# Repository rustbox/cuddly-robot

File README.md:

# cuddly-robot

setup: install [minipro](https://gitlab.com/DavidGriffith/minipro)

flash me with `make generate && minipro -p ATF22V10C -w GAL22V10_fifo_buf.jed`

https://www.proto-advantage.com/store/product_info.php?products_id=2200264

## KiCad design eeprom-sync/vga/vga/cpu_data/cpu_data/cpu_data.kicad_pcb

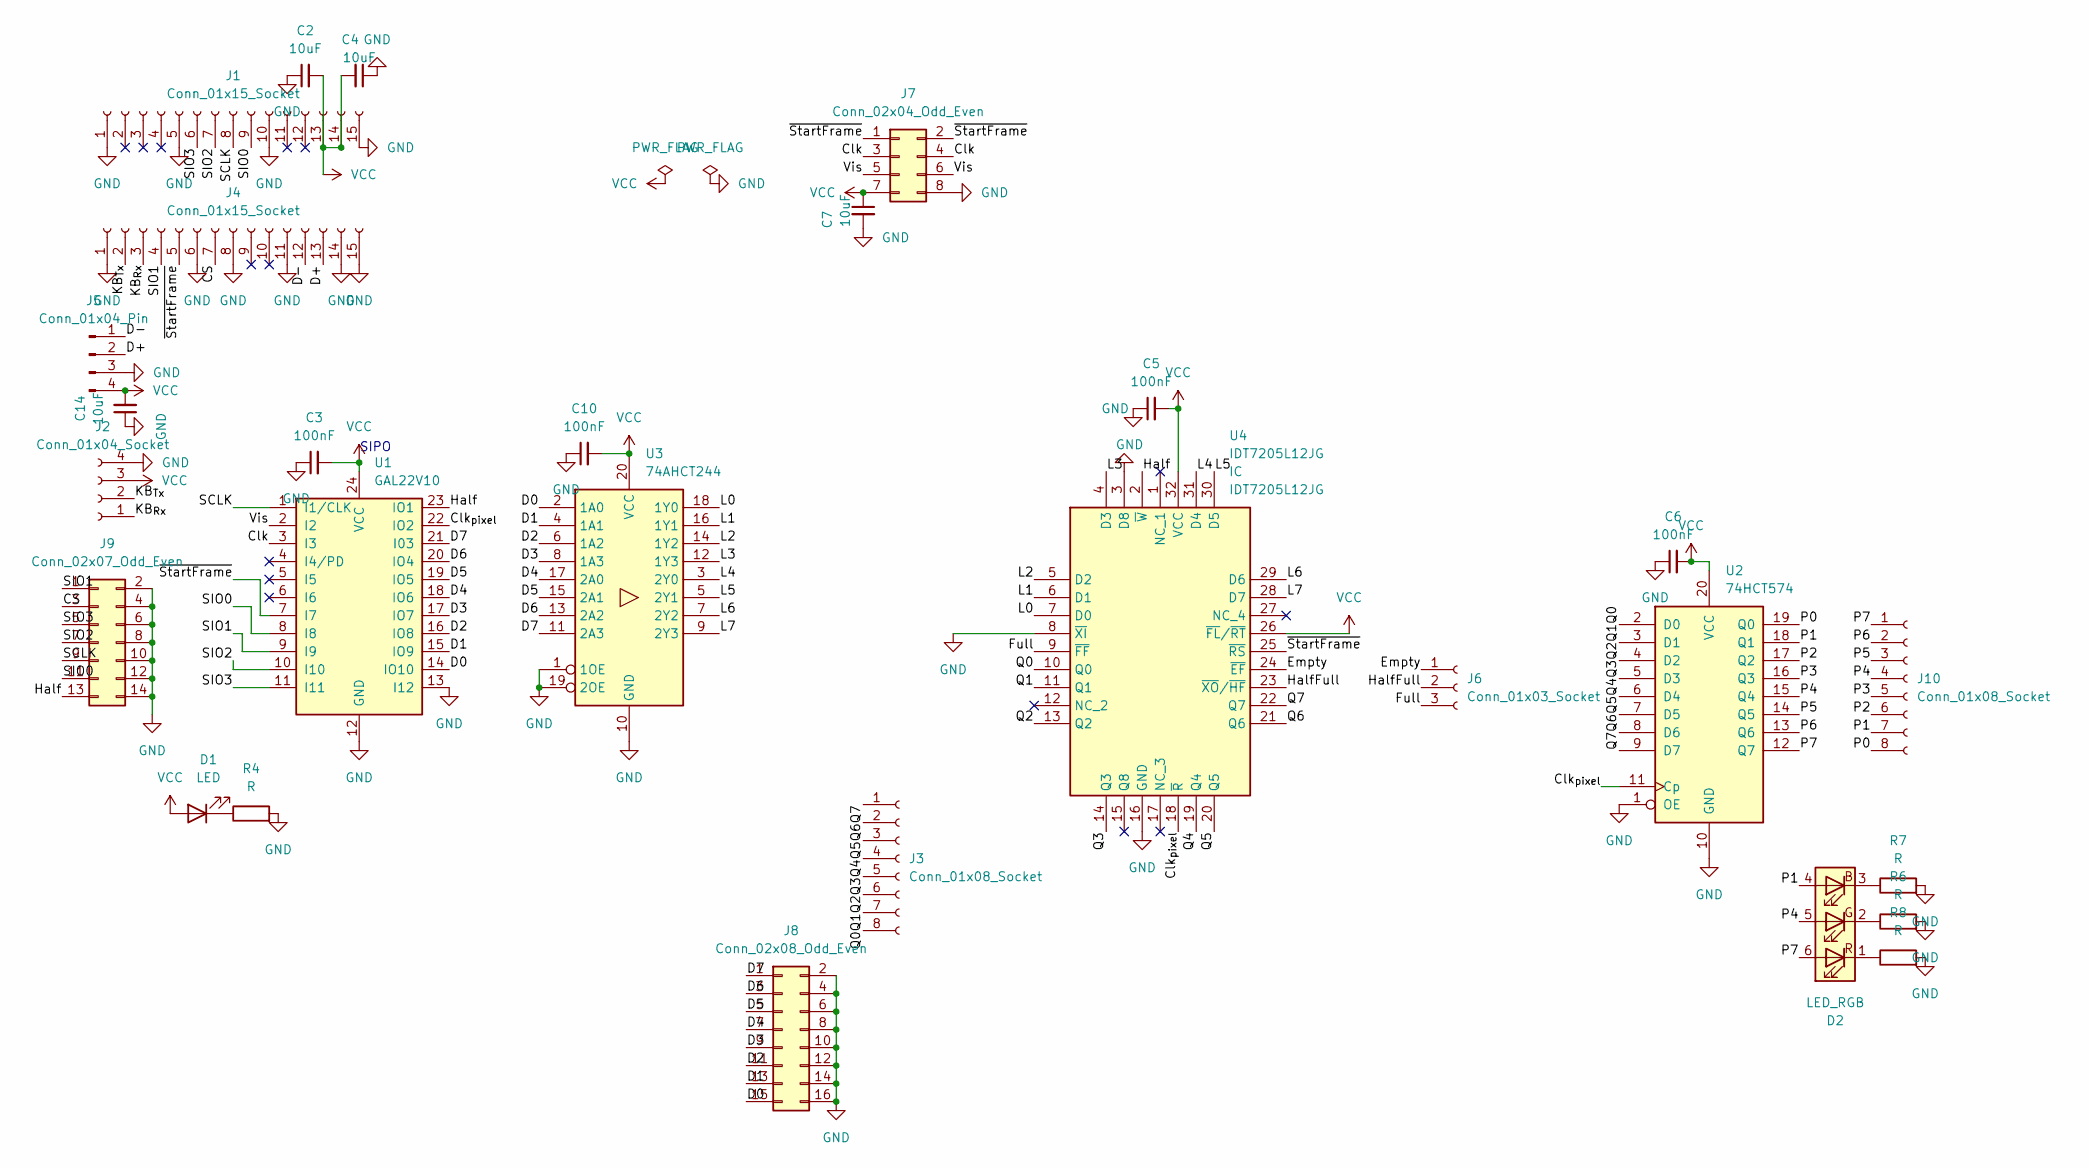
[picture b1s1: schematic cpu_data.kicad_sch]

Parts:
C2, C4, C7, C14: 10uF; C_0805_2012Metric_Pad1.18x1.45mm_HandSolder
C3, C5, C6, C10: 100nF; C_0805_2012Metric_Pad1.18x1.45mm_HandSolder
D1: LED; LED_0805_2012Metric_Pad1.15x1.40mm_HandSolder
D2: LED_RGB; LED_Avago_PLCC6_3x2.8mm
J1, J4: Conn_01x15_Socket; PinSocket_1x15_P2.54mm_Vertical
J2: Conn_01x04_Socket; PinSocket_1x04_P2.54mm_Vertical
J3: Conn_01x08_Socket; PinHeader_1x08_P2.54mm_Vertical
J5: Conn_01x04_Pin; PinHeader_1x04_P2.54mm_Vertical
J6: Conn_01x03_Socket; PinSocket_1x03_P2.54mm_Vertical
J7: Conn_02x04_Odd_Even; PinSocket_2x04_P2.54mm_Vertical
J8: Conn_02x08_Odd_Even; PinHeader_2x08_P2.54mm_Vertical
J9: Conn_02x07_Odd_Even; PinHeader_2x07_P2.54mm_Vertical
J10: Conn_01x08_Socket; PinSocket_1x08_P2.54mm_Vertical
R4, R6, R7, R8: R; R_0805_2012Metric_Pad1.20x1.40mm_HandSolder
U1: GAL22V10; DIP-24_W7.62mm_Socket
U2: 74HCT574; SOIC-20W_7.5x12.8mm_P1.27mm
U3: 74AHCT244; TSSOP-20_4.4x6.5mm_P0.65mm
U4: IDT7205L12JG; plcc32-socket; Manufacturer_Part_Number IDT7205L12JG

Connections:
/CS: J4.7, J9.3
/Clk: J7.3, J7.4, U1.3 (I3)
/Clk_{pixel}: U1.22 (IO2), U2.11 (Cp), U4.18 (~R)
/D0: J8.15, U1.14 (IO10), U3.2 (1A0)
/D1: J8.13, U1.15 (IO9), U3.4 (1A1)
/D2: J8.11, U1.16 (IO8), U3.6 (1A2)
/D3: J8.9, U1.17 (IO7), U3.8 (1A3)
/D4: J8.7, U1.18 (IO6), U3.17 (2A0)
/D5: J8.5, U1.19 (IO5), U3.15 (2A1)
/D6: J8.3, U1.20 (IO4), U3.13 (2A2)
/D7: J8.1, U1.21 (I03), U3.11 (2A3)
/D+: J4.13, J5.2
/D-: J4.12, J5.1
/Empty: J6.1, U4.24 (~EF)
/Full: J6.3, U4.9 (~FF)
/Half: J9.13, U1.23 (IO1), U4.2 (~W)
/HalfFull: J6.2, U4.23 (~XO/~HF)
/KB_{Rx}: J2.1, J4.3
/KB_{Tx}: J2.2, J4.2
/L0: U3.18 (1Y0), U4.7 (D0)
/L1: U3.16 (1Y1), U4.6 (D1)
/L2: U3.14 (1Y2), U4.5 (D2)
/L3: U3.12 (1Y3), U4.4 (D3)
/L4: U3.3 (2Y0), U4.31 (D4)
/L5: U3.5 (2Y1), U4.30 (D5)
/L6: U3.7 (2Y2), U4.29 (D6)
/L7: U3.9 (2Y3), U4.28 (D7)
/P0: J10.8, U2.19 (Q0)
/P1: D2.4 (BA), J10.7, U2.18 (Q1)
/P2: J10.6, U2.17 (Q2)
/P3: J10.5, U2.16 (Q3)
/P4: D2.5 (GA), J10.4, U2.15 (Q4)
/P5: J10.3, U2.14 (Q5)
/P6: J10.2, U2.13 (Q6)
/P7: D2.6 (RA), J10.1, U2.12 (Q7)
/Q0: J3.8, U2.2 (D0), U4.10 (Q0)
/Q1: J3.7, U2.3 (D1), U4.11 (Q1)
/Q2: J3.6, U2.4 (D2), U4.13 (Q2)
/Q3: J3.5, U2.5 (D3), U4.14 (Q3)
/Q4: J3.4, U2.6 (D4), U4.19 (Q4)
/Q5: J3.3, U2.7 (D5), U4.20 (Q5)
/Q6: J3.2, U2.8 (D6), U4.21 (Q6)
/Q7: J3.1, U2.9 (D7), U4.22 (Q7)
/SCLK: J1.8, J9.9, U1.1 (I1/CLK)
/SIO0: J1.9, J9.11, U1.8 (I8)
/SIO1: J4.4, J9.1, U1.9 (I9)
/SIO2: J1.7, J9.7, U1.10 (I10)
/SIO3: J1.6, J9.5, U1.11 (I11)
/Vis: J7.5, J7.6, U1.2 (I2)
/~StartFrame: J4.5, J7.1, J7.2, U1.7 (I7), U4.25 (~RS)
GND: C2.1, C3.1, C4.1, C5.1, C6.1, C7.2, C10.1, C14.1, J1.1, J1.5, J1.10, J1.15, J2.4, J4.1, J4.6, J4.8, J4.11, J4.14, J4.15, J5.3, J7.8, J8.2, J8.4, J8.6, J8.8, J8.10, J8.12, J8.14, J8.16, J9.2, J9.4, J9.6, J9.8, J9.10, J9.12, J9.14, R4.2, R6.2, R7.2, R8.2, U1.12 (GND), U1.13 (I12), U2.1 (OE), U2.10 (GND), U3.1 (1OE), U3.10 (GND), U3.19 (2OE), U4.3 (D8), U4.8 (~XI), U4.16 (GND)
unnamed: D1.1 (K), R4.1
unnamed: D2.3 (BK), R7.1
unnamed: D2.2 (GK), R6.1
unnamed: D2.1 (RK), R8.1
VCC: C2.2, C3.2, C4.2, C5.2, C6.2, C7.1, C10.2, C14.2, D1.2 (A), J1.13, J1.14, J2.3, J5.4, J7.7, U1.24 (VCC), U2.20 (VCC), U3.20 (VCC), U4.26 (~FL/~RT), U4.32 (VCC)

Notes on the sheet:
SIPO

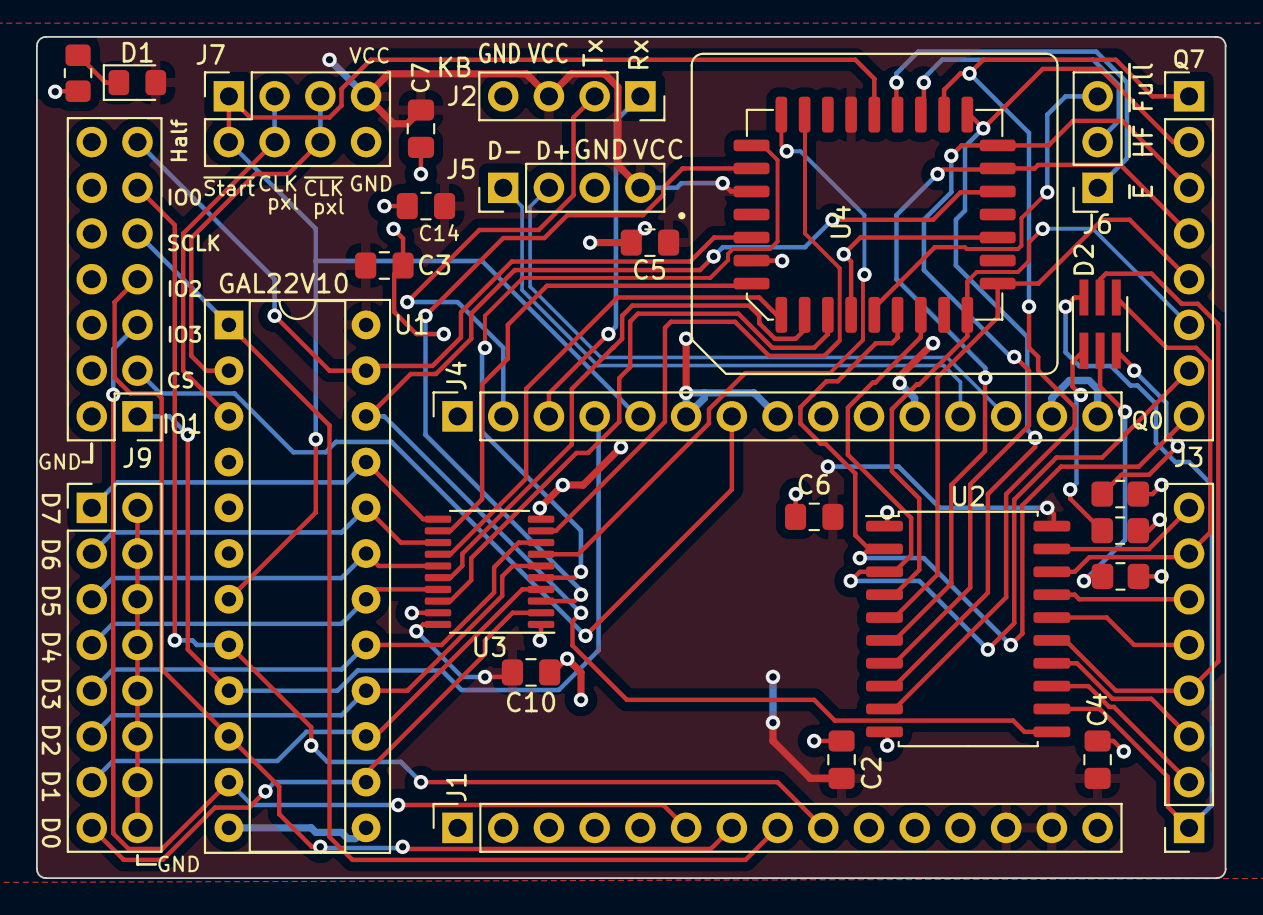
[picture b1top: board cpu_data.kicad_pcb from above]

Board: 2 copper layers, 66.0 x 46.7 mm, 28 parts (0 on the bottom side), 56 nets.

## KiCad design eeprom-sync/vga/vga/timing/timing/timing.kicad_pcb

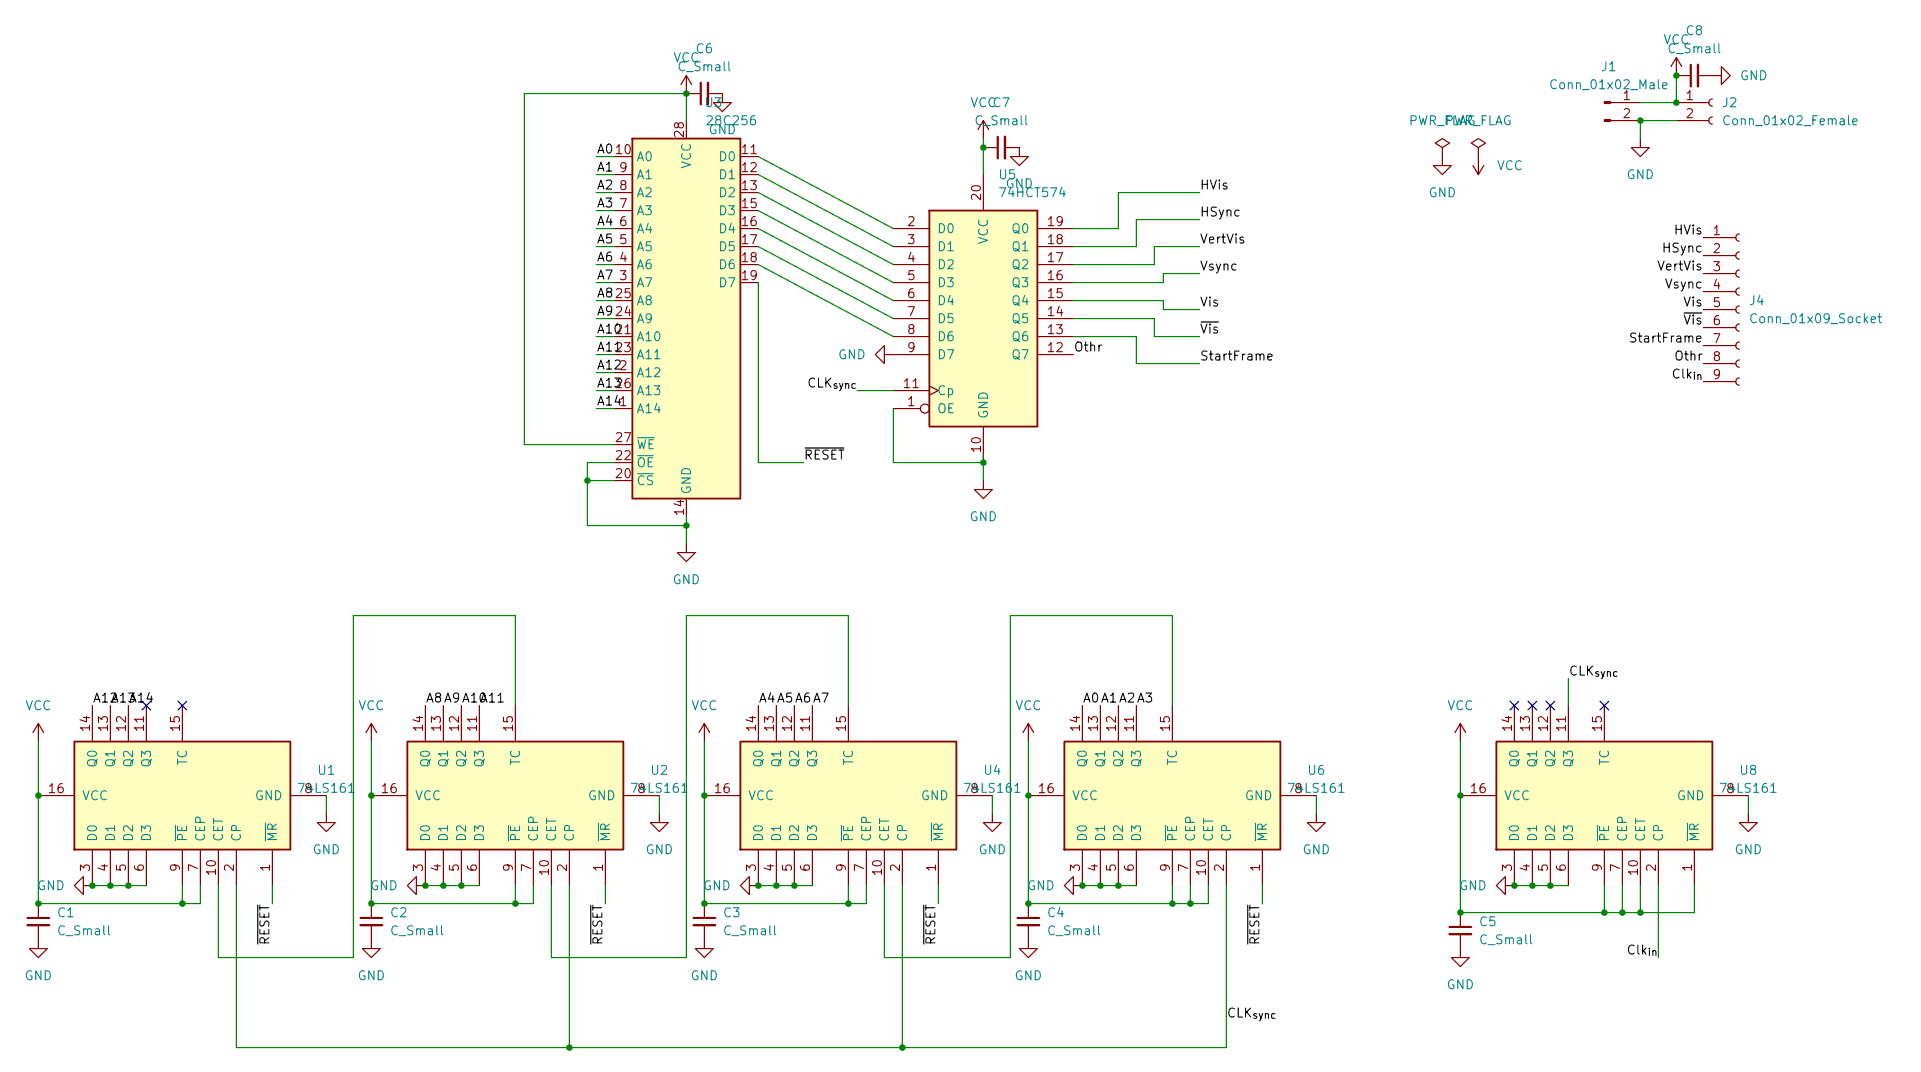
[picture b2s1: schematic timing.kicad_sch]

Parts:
C1, C2, C3, C4, C5, C6, C7, C8: C_Small; C_0805_2012Metric_Pad1.18x1.45mm_HandSolder
J1: Conn_01x02_Male; PinHeader_1x02_P2.54mm_Vertical
J2: Conn_01x02_Female; PinSocket_1x02_P2.54mm_Vertical
J4: Conn_01x09_Socket; PinSocket_1x09_P2.54mm_Vertical
U1, U2, U4, U6, U8: 74LS161; SOIC-16_3.9x9.9mm_P1.27mm
U3: 28C256; DIP-28_W15.24mm_Socket
U5: 74HCT574; SOIC-20W_7.5x12.8mm_P1.27mm

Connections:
/A0: U3.10 (A0), U6.14 (Q0)
/A1: U3.9 (A1), U6.13 (Q1)
/A2: U3.8 (A2), U6.12 (Q2)
/A3: U3.7 (A3), U6.11 (Q3)
/A4: U3.6 (A4), U4.14 (Q0)
/A5: U3.5 (A5), U4.13 (Q1)
/A6: U3.4 (A6), U4.12 (Q2)
/A7: U3.3 (A7), U4.11 (Q3)
/A8: U2.14 (Q0), U3.25 (A8)
/A9: U2.13 (Q1), U3.24 (A9)
/A10: U2.12 (Q2), U3.21 (A10)
/A11: U2.11 (Q3), U3.23 (A11)
/A12: U1.14 (Q0), U3.2 (A12)
/A13: U1.13 (Q1), U3.26 (A13)
/A14: U1.12 (Q2), U3.1 (A14)
/CLK_{sync}: U1.2 (CP), U2.2 (CP), U4.2 (CP), U5.11 (Cp), U6.2 (CP), U8.11 (Q3)
/Clk_{in}: J4.9, U8.2 (CP)
/HSync: J4.2, U5.18 (Q1)
/HVis: J4.1, U5.19 (Q0)
/Othr: J4.8, U5.12 (Q7)
/StartFrame: J4.7, U5.13 (Q6)
/VertVis: J4.3, U5.17 (Q2)
/Vis: J4.5, U5.15 (Q4)
/Vsync: J4.4, U5.16 (Q3)
/~RESET: U1.1 (~MR), U2.1 (~MR), U3.19 (D7), U4.1 (~MR), U6.1 (~MR)
/~Vis: J4.6, U5.14 (Q5)
GND: C1.2, C2.2, C3.2, C4.2, C5.2, C6.2, C7.2, C8.2, J1.2, J2.2, U1.3 (D0), U1.4 (D1), U1.5 (D2), U1.6 (D3), U1.8 (GND), U2.3 (D0), U2.4 (D1), U2.5 (D2), U2.6 (D3), U2.8 (GND), U3.14 (GND), U3.20 (~CS), U3.22 (~OE), U4.3 (D0), U4.4 (D1), U4.5 (D2), U4.6 (D3), U4.8 (GND), U5.1 (OE), U5.9 (D7), U5.10 (GND), U6.3 (D0), U6.4 (D1), U6.5 (D2), U6.6 (D3), U6.8 (GND), U8.3 (D0), U8.4 (D1), U8.5 (D2), U8.6 (D3), U8.8 (GND)
unnamed: U1.10 (CET), U2.15 (TC)
unnamed: U2.10 (CET), U4.15 (TC)
unnamed: U3.11 (D0), U5.2 (D0)
unnamed: U3.12 (D1), U5.3 (D1)
unnamed: U3.13 (D2), U5.4 (D2)
unnamed: U3.15 (D3), U5.5 (D3)
unnamed: U3.16 (D4), U5.6 (D4)
unnamed: U3.17 (D5), U5.7 (D5)
unnamed: U3.18 (D6), U5.8 (D6)
unnamed: U4.10 (CET), U6.15 (TC)
VCC: C1.1, C2.1, C3.1, C4.1, C5.1, C6.1, C7.1, C8.1, J1.1, J2.1, U1.7 (CEP), U1.9 (~PE), U1.16 (VCC), U2.7 (CEP), U2.9 (~PE), U2.16 (VCC), U3.27 (~WE), U3.28 (VCC), U4.7 (CEP), U4.9 (~PE), U4.16 (VCC), U5.20 (VCC), U6.7 (CEP), U6.9 (~PE), U6.10 (CET), U6.16 (VCC), U8.1 (~MR), U8.7 (CEP), U8.9 (~PE), U8.10 (CET), U8.16 (VCC)

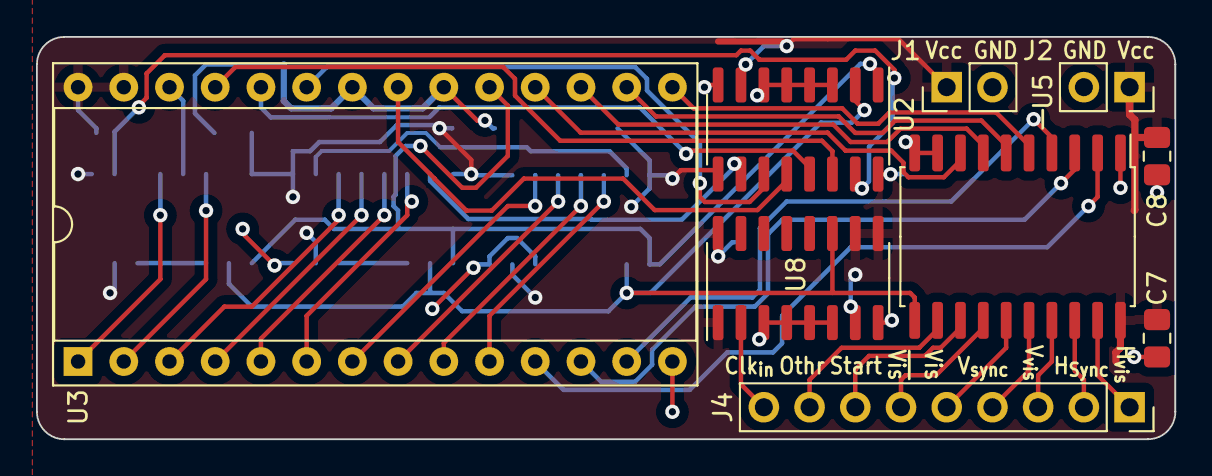
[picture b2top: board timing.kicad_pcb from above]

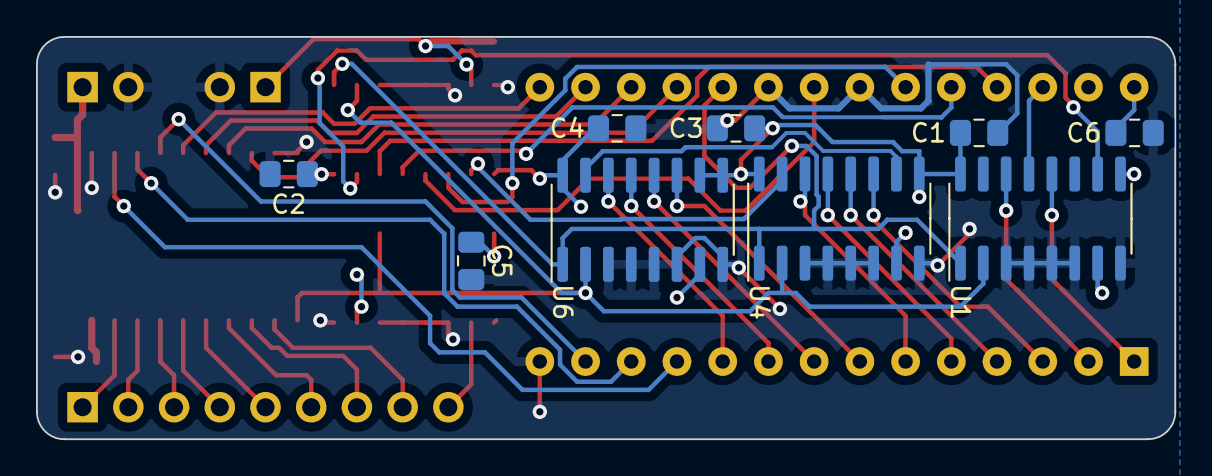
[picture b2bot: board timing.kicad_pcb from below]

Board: 2 copper layers, 63.2 x 22.4 mm, 18 parts (9 on the bottom side), 38 nets.

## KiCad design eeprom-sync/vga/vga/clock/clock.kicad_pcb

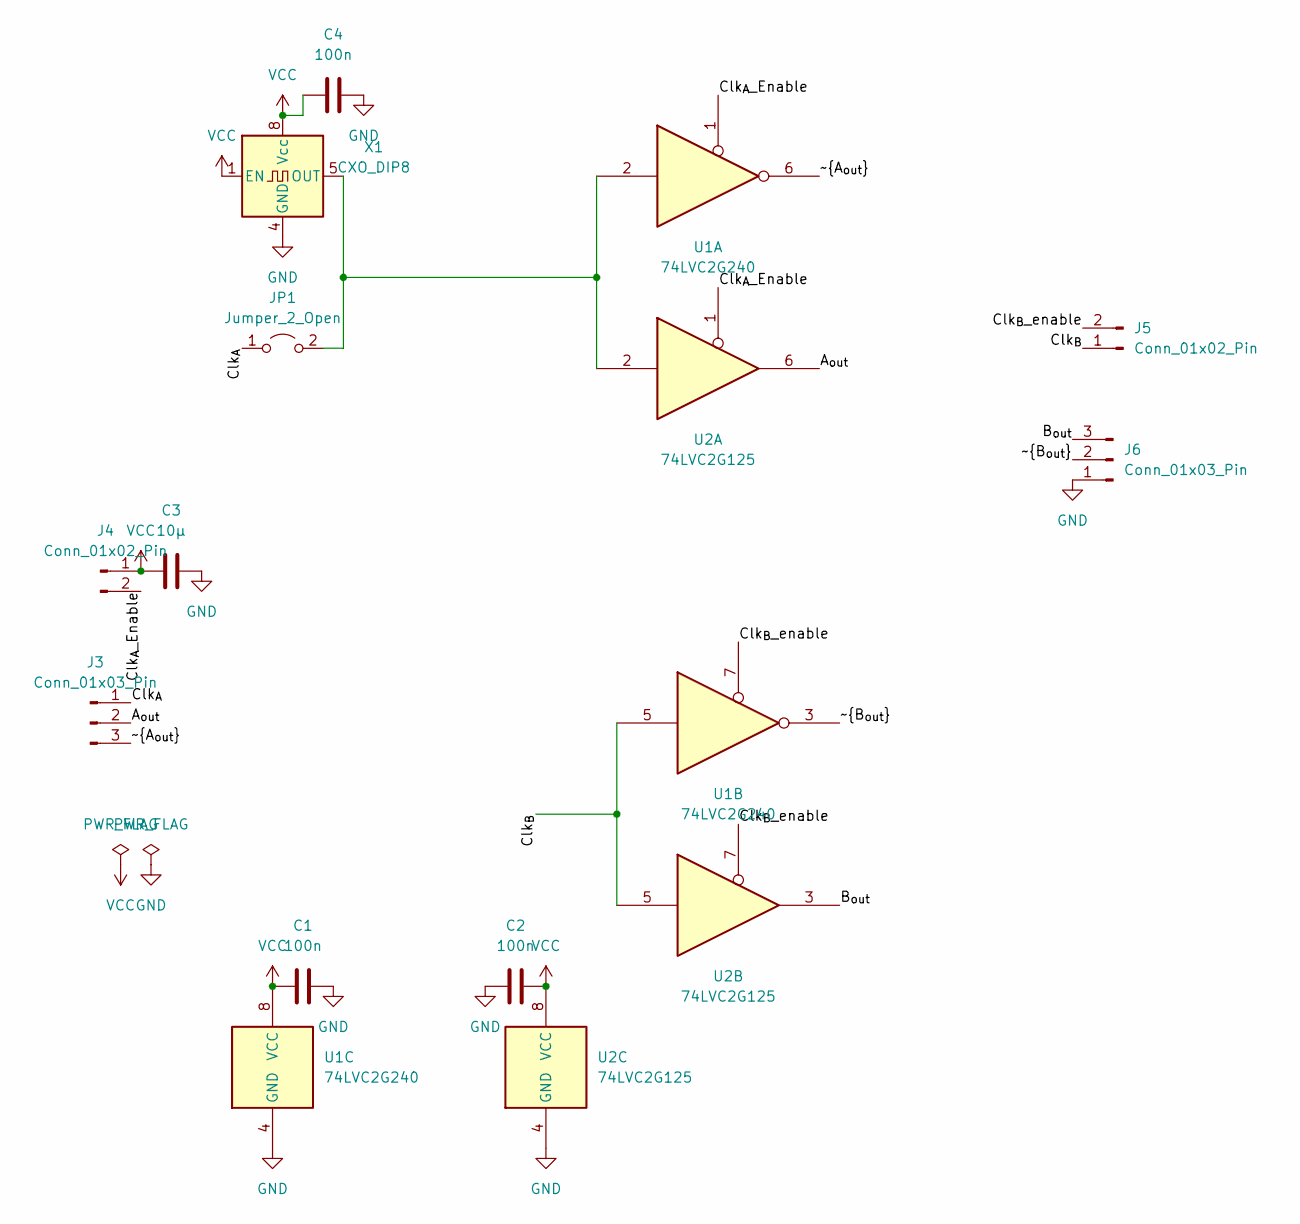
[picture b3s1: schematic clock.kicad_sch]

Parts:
C1, C2, C4: 100n; C_0805_2012Metric_Pad1.18x1.45mm_HandSolder
C3: 10µ; C_0805_2012Metric_Pad1.18x1.45mm_HandSolder
J3, J6: Conn_01x03_Pin; PinHeader_1x03_P2.54mm_Vertical
J4, J5: Conn_01x02_Pin; PinHeader_1x02_P2.54mm_Vertical
JP1: Jumper_2_Open; SolderJumper-2_P1.3mm_Open_RoundedPad1.0x1.5mm
U1: 74LVC2G240; TSSOP-8_3x3mm_P0.65mm
U2: 74LVC2G125; TSSOP-8_3x3mm_P0.65mm
X1: CXO_DIP8; Oscillator_DIP-8

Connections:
/A_{out}: J3.2, U2.6
/B_{out}: J6.3, U2.3
/Clk_{A}: J3.1, JP1.1 (A)
/Clk_{A}_Enable: J4.2, U1.1, U2.1
/Clk_{B}: J5.1, U1.5, U2.5
/Clk_{B}_enable: J5.2, U1.7, U2.7
/~A_{out}: J3.3, U1.6
/~B_{out}: J6.2, U1.3
GND: C1.2, C2.1, C3.2, C4.2, J6.1, U1.4 (GND), U2.4 (GND), X1.4 (GND)
unnamed: JP1.2 (B), U1.2, U2.2, X1.5 (OUT)
VCC: C1.1, C2.2, C3.1, C4.1, J4.1, U1.8 (VCC), U2.8 (VCC), X1.1 (EN), X1.8 (Vcc)

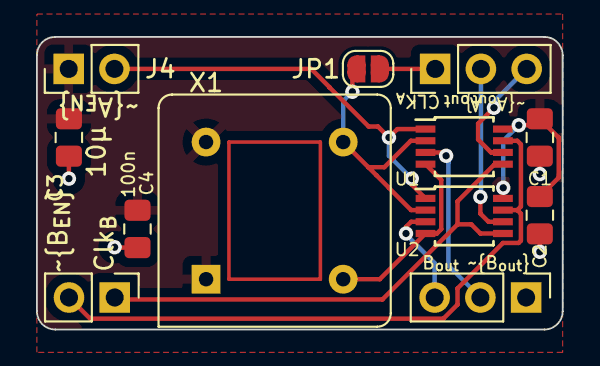
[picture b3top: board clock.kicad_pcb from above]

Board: 2 copper layers, 29.2 x 16.3 mm, 12 parts (0 on the bottom side), 11 nets.

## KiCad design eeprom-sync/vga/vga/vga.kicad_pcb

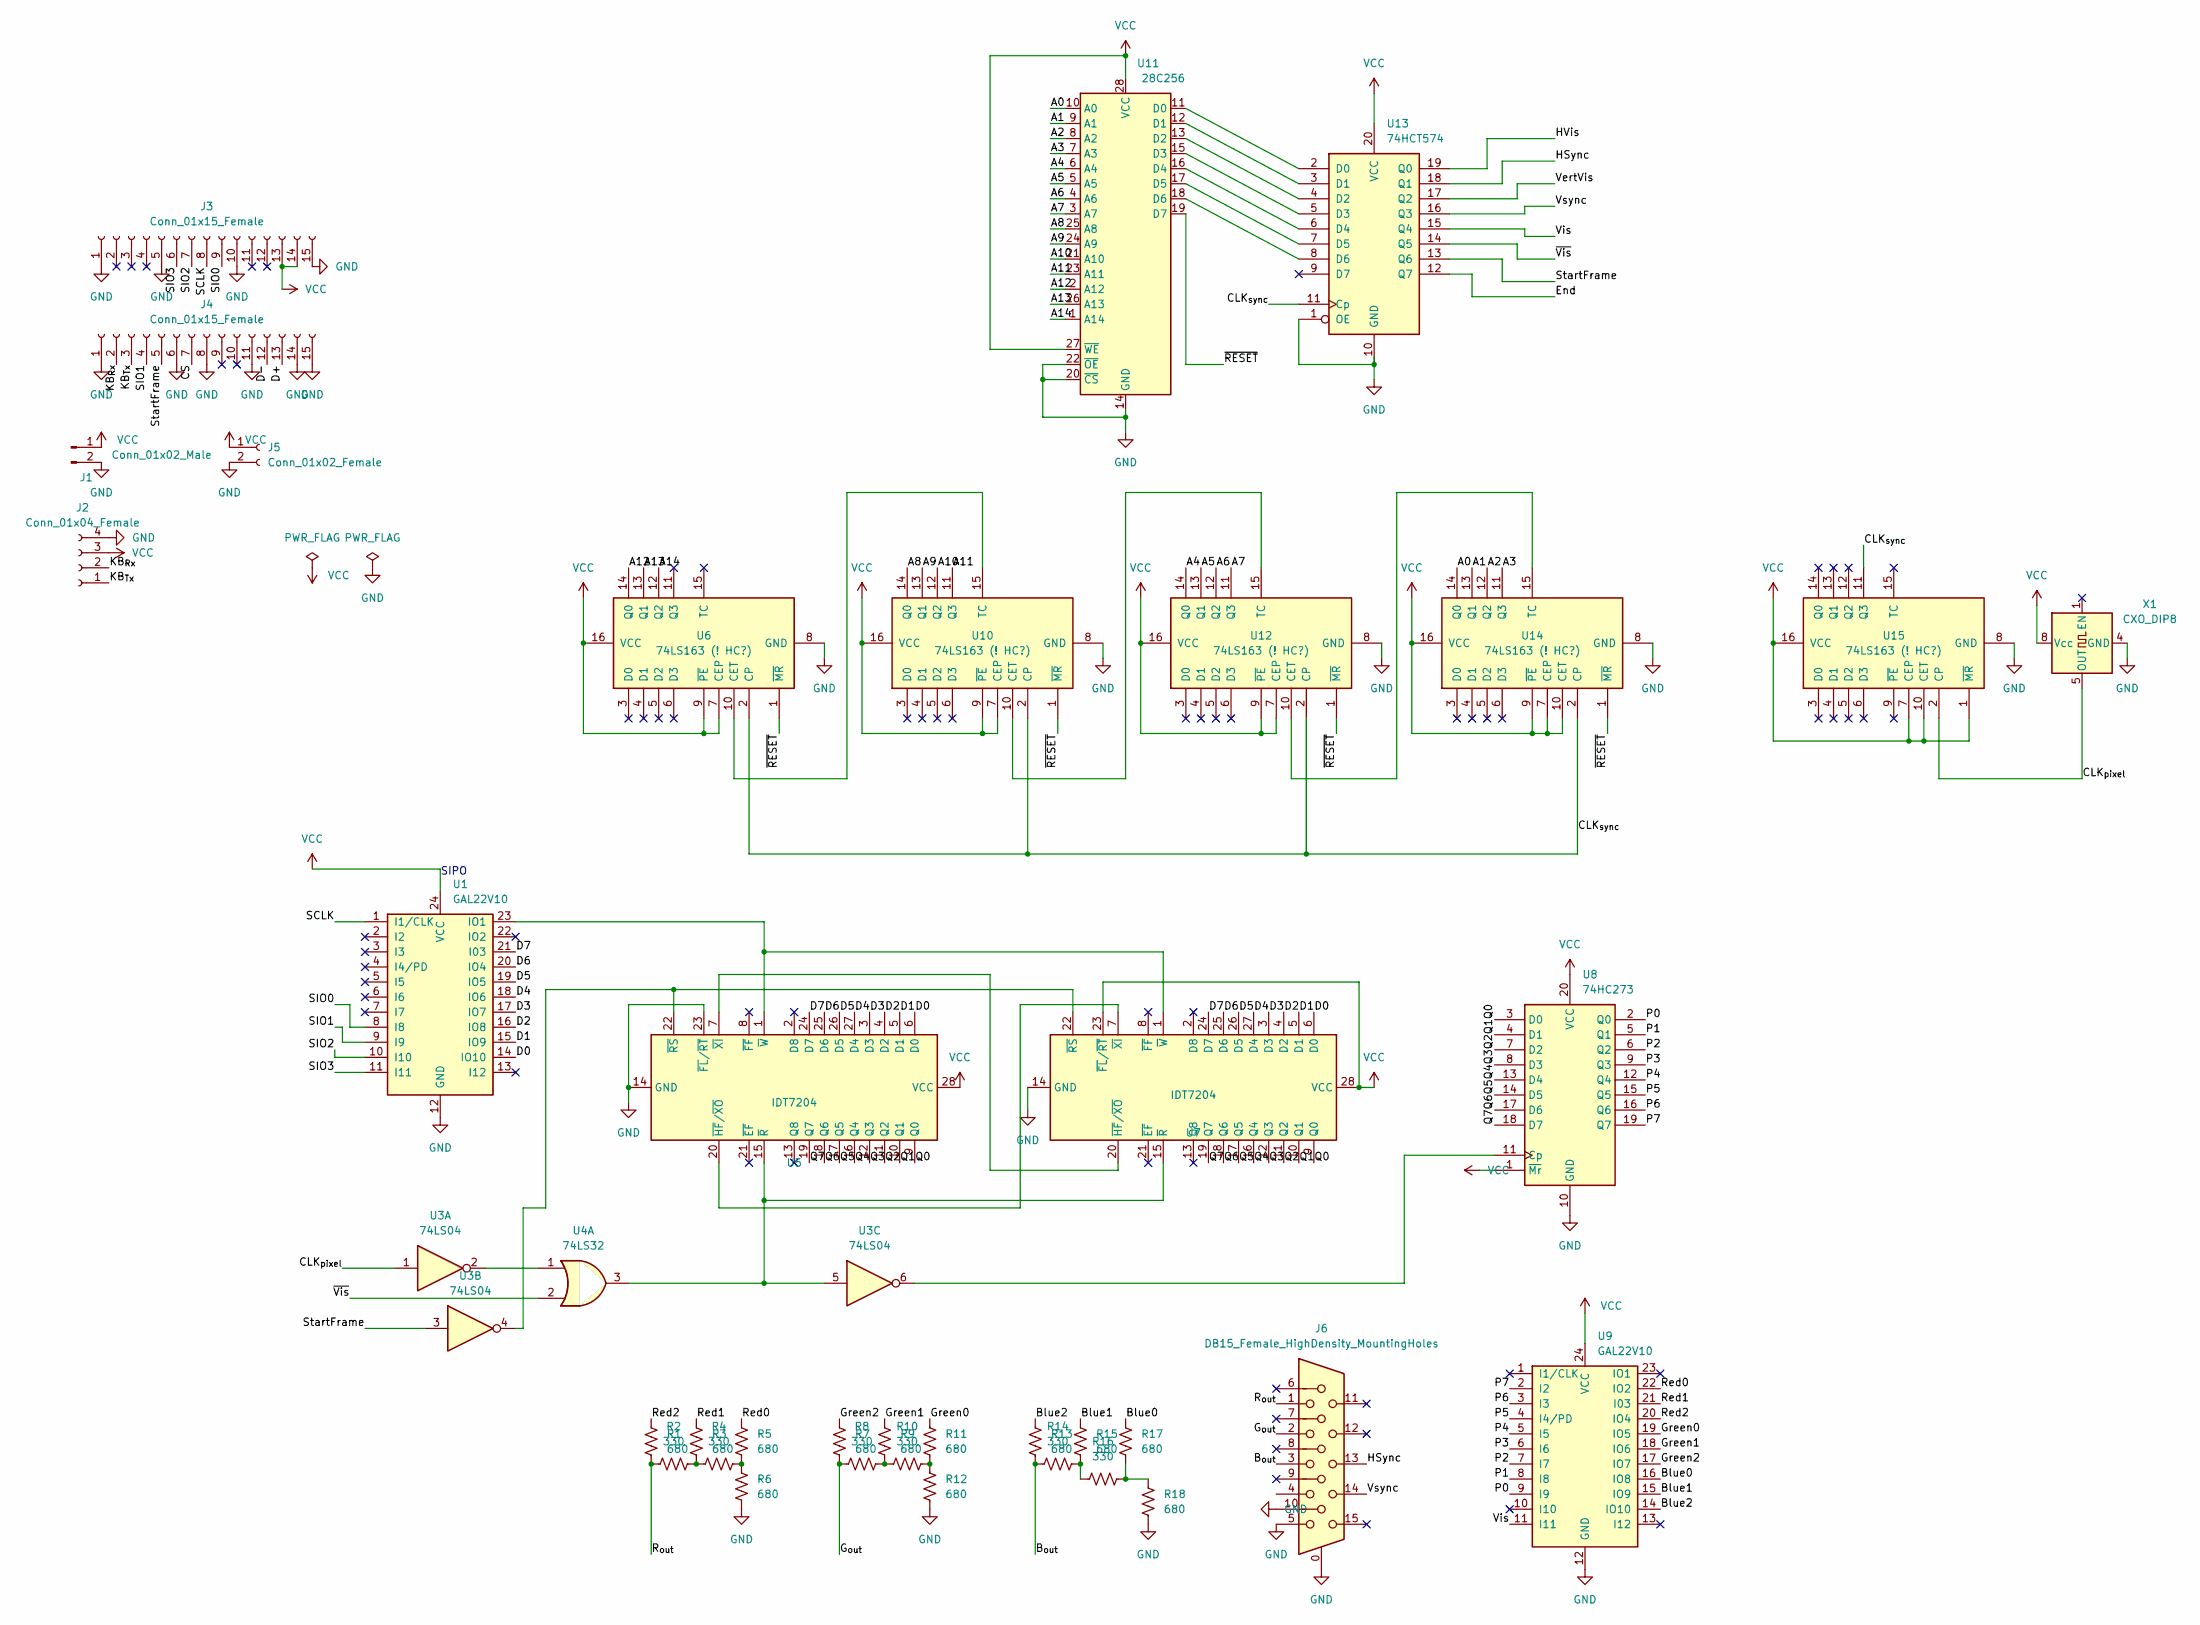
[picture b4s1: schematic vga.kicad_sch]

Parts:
J1: Conn_01x02_Male; PinHeader_1x02_P2.54mm_Vertical
J2: Conn_01x04_Female; PinSocket_1x04_P2.54mm_Vertical
J3, J4: Conn_01x15_Female; PinSocket_1x15_P2.54mm_Vertical
J5: Conn_01x02_Female; PinSocket_1x02_P2.54mm_Vertical
J6: DB15_Female_HighDensity_MountingHoles; DSUB-15_Female_Horizontal_P2.77x2.84mm_EdgePinOffset4.94mm_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
R1, R3, R5, R6, R7, R9, R11, R12, R13, R15, R17, R18: 680; R_Axial_DIN0204_L3.6mm_D1.6mm_P5.08mm_Horizontal
R2, R4, R8, R10, R14, R16: 330; R_Axial_DIN0204_L3.6mm_D1.6mm_P5.08mm_Horizontal
U1, U9: GAL22V10; DIP-24_W7.62mm_Socket
U3: 74LS04; DIP-14_W7.62mm
U4: 74LS32; DIP-14_W7.62mm
U5, U7: IDT7204; DIP-28_W7.62mm
U6, U10, U12, U14, U15: 74LS163 (! HC?); DIP-16_W7.62mm
U8: 74HC273; DIP-20_W7.62mm
U11: 28C256; DIP-28_W15.24mm_Socket
U13: 74HCT574; DIP-20_W7.62mm
X1: CXO_DIP8; Oscillator_DIP-8

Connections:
/A0: U11.10 (A0), U14.14 (Q0)
/A1: U11.9 (A1), U14.13 (Q1)
/A2: U11.8 (A2), U14.12 (Q2)
/A3: U11.7 (A3), U14.11 (Q3)
/A4: U11.6 (A4), U12.14 (Q0)
/A5: U11.5 (A5), U12.13 (Q1)
/A6: U11.4 (A6), U12.12 (Q2)
/A7: U11.3 (A7), U12.11 (Q3)
/A8: U10.14 (Q0), U11.25 (A8)
/A9: U10.13 (Q1), U11.24 (A9)
/A10: U10.12 (Q2), U11.21 (A10)
/A11: U10.11 (Q3), U11.23 (A11)
/A12: U6.14 (Q0), U11.2 (A12)
/A13: U6.13 (Q1), U11.26 (A13)
/A14: U6.12 (Q2), U11.1 (A14)
/B_{out}: J6.3, R13.2, R14.2
/Blue0: R17.1, U9.16 (IO8)
/Blue1: R15.1, U9.15 (IO9)
/Blue2: R13.1, U9.14 (IO10)
/CLK_{pixel}: U3.1, U15.2 (CP), X1.5 (OUT)
/CLK_{sync}: U6.2 (CP), U10.2 (CP), U12.2 (CP), U13.11 (Cp), U14.2 (CP), U15.11 (Q3)
/CS: J4.7
/D0: U1.14 (IO10), U5.6 (D0), U7.6 (D0)
/D1: U1.15 (IO9), U5.5 (D1), U7.5 (D1)
/D2: U1.16 (IO8), U5.4 (D2), U7.4 (D2)
/D3: U1.17 (IO7), U5.3 (D3), U7.3 (D3)
/D4: U1.18 (IO6), U5.27 (D4), U7.27 (D4)
/D5: U1.19 (IO5), U5.26 (D5), U7.26 (D5)
/D6: U1.20 (IO4), U5.25 (D6), U7.25 (D6)
/D7: U1.21 (I03), U5.24 (D7), U7.24 (D7)
/D+: J4.13
/D-: J4.12
/End: U13.12 (Q7)
/G_{out}: J6.2, R7.2, R8.2
/Green0: R11.1, U9.19 (IO5)
/Green1: R9.1, U9.18 (IO6)
/Green2: R7.1, U9.17 (IO7)
/HSync: J6.13, U13.18 (Q1)
/HVis: U13.19 (Q0)
/KB_{Rx}: J2.2, J4.2
/KB_{Tx}: J2.1, J4.3
/P0: U8.2 (Q0), U9.9 (I9)
/P1: U8.5 (Q1), U9.8 (I8)
/P2: U8.6 (Q2), U9.7 (I7)
/P3: U8.9 (Q3), U9.6 (I6)
/P4: U8.12 (Q4), U9.5 (I5)
/P5: U8.15 (Q5), U9.4 (I4/PD)
/P6: U8.16 (Q6), U9.3 (I3)
/P7: U8.19 (Q7), U9.2 (I2)
/Q0: U5.9 (Q0), U7.9 (Q0), U8.3 (D0)
/Q1: U5.10 (Q1), U7.10 (Q1), U8.4 (D1)
/Q2: U5.11 (Q2), U7.11 (Q2), U8.7 (D2)
/Q3: U5.12 (Q3), U7.12 (Q3), U8.8 (D3)
/Q4: U5.16 (Q4), U7.16 (Q4), U8.13 (D4)
/Q5: U5.17 (Q5), U7.17 (Q5), U8.14 (D5)
/Q6: U5.18 (Q6), U7.18 (Q6), U8.17 (D6)
/Q7: U5.19 (Q7), U7.19 (Q7), U8.18 (D7)
/R_{out}: J6.1, R1.2, R2.2
/Red0: R5.1, U9.22 (IO2)
/Red1: R3.1, U9.21 (I03)
/Red2: R1.1, U9.20 (IO4)
/SCLK: J3.8, U1.1 (I1/CLK)
/SIO0: J3.9, U1.8 (I8)
/SIO1: J4.4, U1.9 (I9)
/SIO2: J3.7, U1.10 (I10)
/SIO3: J3.6, U1.11 (I11)
/StartFrame: J4.5, U3.3, U13.13 (Q6)
/VertVis: U13.17 (Q2)
/Vis: U9.11 (I11), U13.15 (Q4)
/Vsync: J6.14, U13.16 (Q3)
/~RESET: U6.1 (~MR), U10.1 (~MR), U11.19 (D7), U12.1 (~MR), U14.1 (~MR)
/~Vis: U4.2, U13.14 (Q5)
GND: J1.2, J2.4, J3.1, J3.5, J3.10, J3.15, J4.1, J4.6, J4.8, J4.11, J4.14, J4.15, J5.2, J6.0, J6.5, J6.10, R6.1, R12.1, R18.1, U1.12 (GND), U5.14 (GND), U5.23 (~FL/~RT), U6.8 (GND), U7.14 (GND), U8.10 (GND), U9.12 (GND), U10.8 (GND), U11.14 (GND), U11.20 (~CS), U11.22 (~OE), U12.8 (GND), U13.1 (OE), U13.10 (GND), U14.8 (GND), U15.8 (GND), X1.4 (GND)
unnamed: R2.1, R3.2, R4.1
unnamed: R4.2, R5.2, R6.2
unnamed: R8.1, R9.2, R10.1
unnamed: R10.2, R11.2, R12.2
unnamed: R14.1, R15.2, R16.1
unnamed: R16.2, R17.2, R18.2
unnamed: U1.23 (IO1), U5.1 (~W), U7.1 (~W)
unnamed: U3.2, U4.1
unnamed: U3.5, U4.3, U5.15 (~R), U7.15 (~R)
unnamed: U5.7 (~XI), U7.20 (~HF/~XO)
unnamed: U5.20 (~HF/~XO), U7.7 (~XI)
unnamed: U3.4, U5.22 (~RS), U7.22 (~RS)
unnamed: U3.6, U8.11 (Cp)
unnamed: U10.10 (CET), U12.15 (TC)
unnamed: U6.10 (CET), U10.15 (TC)
unnamed: U11.11 (D0), U13.2 (D0)
unnamed: U11.12 (D1), U13.3 (D1)
unnamed: U11.13 (D2), U13.4 (D2)
unnamed: U11.15 (D3), U13.5 (D3)
unnamed: U11.16 (D4), U13.6 (D4)
unnamed: U11.17 (D5), U13.7 (D5)
unnamed: U11.18 (D6), U13.8 (D6)
unnamed: U12.10 (CET), U14.15 (TC)
VCC: J1.1, J2.3, J3.13, J3.14, J5.1, U1.24 (VCC), U5.28 (VCC), U6.7 (CEP), U6.9 (~PE), U6.16 (VCC), U7.23 (~FL/~RT), U7.28 (VCC), U8.1 (~Mr), U8.20 (VCC), U9.24 (VCC), U10.7 (CEP), U10.9 (~PE), U10.16 (VCC), U11.27 (~WE), U11.28 (VCC), U12.7 (CEP), U12.9 (~PE), U12.16 (VCC), U13.20 (VCC), U14.7 (CEP), U14.9 (~PE), U14.10 (CET), U14.16 (VCC), U15.1 (~MR), U15.7 (CEP), U15.10 (CET), U15.16 (VCC), X1.8 (Vcc)

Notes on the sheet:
SIPO

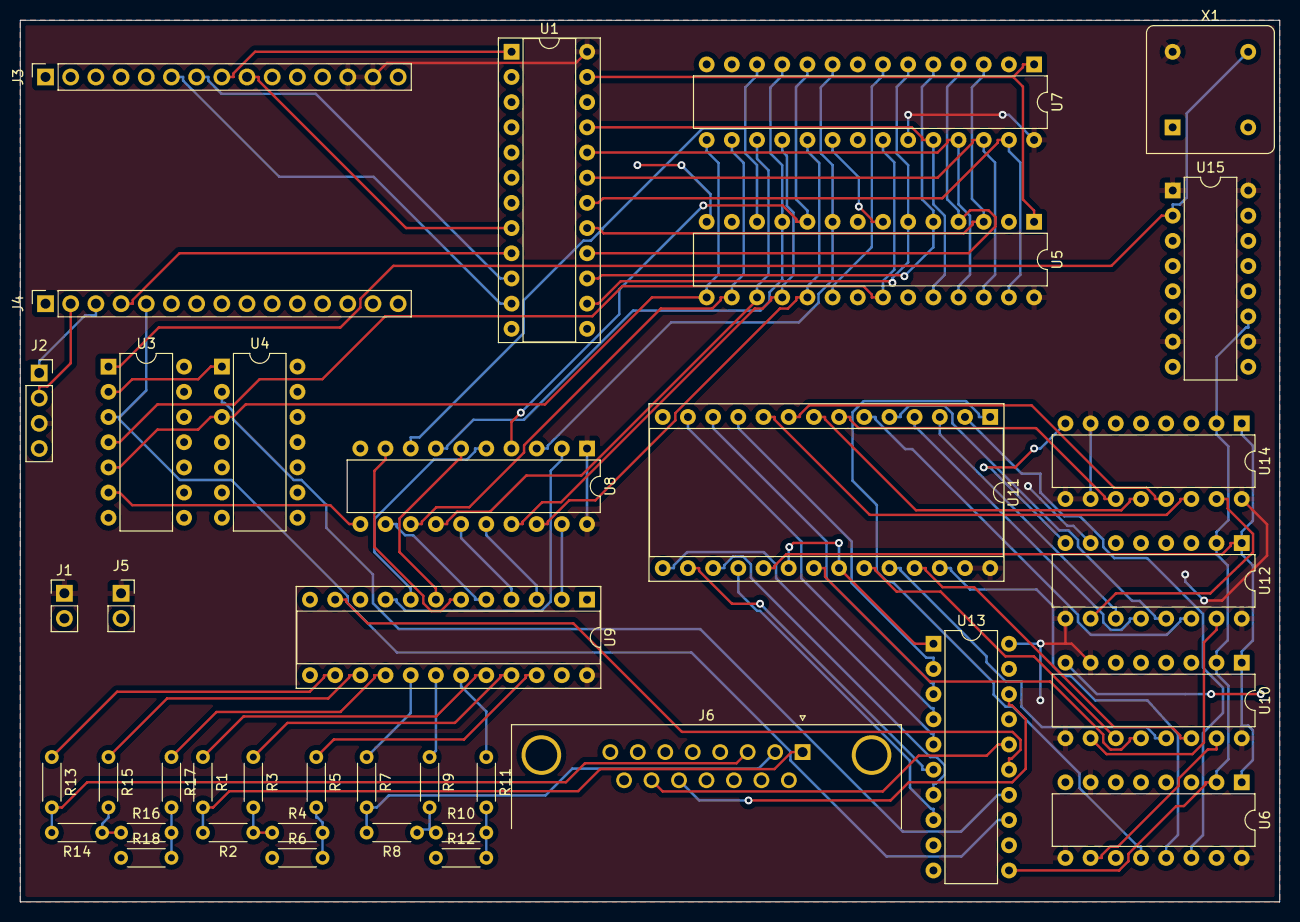
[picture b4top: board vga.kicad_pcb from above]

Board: 2 copper layers, 127.0 x 88.9 mm, 39 parts (0 on the bottom side), 91 nets.

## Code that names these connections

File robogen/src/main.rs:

use std::io::Write;

use bitflags::bitflags;

bitflags! {
    /// This is state of the vga timing at some "wide" pixel column.
    /// The states expressed here are all in terms of "active high"
    /// to make the logic easier to understand. 
    /// For example, at pixel 0 is horizontally visible, so HVIS is set.
    /// At pixel 41 it's in the blanking area (not visible) but the
    /// horizontal sync pulse should be active, so HVIS is not set and
    /// HSYNC is set.
    struct PixelState: u8 {
        const HVIS = 1;
        const HSYNC = 1 << 1;
        const VVIS = 1 << 2;
        const VSYNC = 1 << 3;
        const FRAME_VIS = 1 << 4;
        const FRAME_NOT_VIS = 1 << 5;
        const START_FRAME_WRITE = 1 << 6;
        const END = 1 << 7;
    }
}

impl PixelState {
    /// These are the bits that are active low. So when converting to a byte
    /// we can flip the bits into an active low domain, rather than the active high
    fn active_low() -> PixelState {
        PixelState::HSYNC | PixelState::VSYNC | PixelState::END
    }
}


impl Default for PixelState {
    fn default() -> Self {
        PixelState::HVIS | PixelState::VVIS
    }
}

impl From<PixelState> for u8 {
    fn from(p: PixelState) -> u8 {
        (PixelState::active_low() ^ p).bits()
    }
}

const WIDTH: usize = 800 / 16;
const HEIGHT: usize = 525;

fn main() {
    let mut timing = [PixelState::default(); WIDTH * HEIGHT];

    for line in 0..HEIGHT {
        for pixel in 0..WIDTH {
            let i = line * WIDTH + pixel;

            let mut state = PixelState::empty();
            state.set(PixelState::HVIS, pixel < 40);
            state.set(PixelState::HSYNC, pixel >= 41 && pixel < 47);
            state.set(PixelState::VVIS, line >= 40 && line < 440);
            state.set(PixelState::VSYNC, line >= 490 && line < 492);
            state.set(PixelState::FRAME_VIS, state.contains(PixelState::HVIS) && state.contains(PixelState::VVIS));
            state.set(PixelState::FRAME_NOT_VIS, !state.contains(PixelState::FRAME_VIS));
            state.set(PixelState::START_FRAME_WRITE, i != 1488);
            state.set(PixelState::END, i == WIDTH * HEIGHT - 1);
            
            let mut repchar = '_';
            if state.contains(PixelState::FRAME_VIS) {
                repchar = '.';
            }

            if state.contains(PixelState::HSYNC) || state.contains(PixelState::VSYNC) {
                repchar = '^';
            }

            if state.contains(PixelState::END) {
                repchar = 'x';
            }

            if !state.contains(PixelState::START_FRAME_WRITE) {
                repchar = '*'
            }

            eprint!("{}", repchar);
            timing[i] = state;
        }
        eprintln!();
    }
    // timing[WIDTH * HEIGHT] = PixelState::END;

    eprintln!("end: {}", timing[WIDTH * HEIGHT - 1].bits);

    let mut prom_file = [0xff as u8; 32768];
    for i in 0..timing.len() {
        prom_file[i] = timing[i].into();
    }

    let _ = std::io::stdout().write_all(&prom_file);

}

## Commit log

2022-08-14 vertical and horizontal timing chips as GAL16V8_horizontal and GAL16V8_vertical and all associated files
2022-08-28 fifo_buf: * renamed the Q pin to Half to indicate the half clock * added the Rdy pin to indicate when the loaded data can be taken * comment explaining the Rdy line color: * color GAL is what will be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
2022-08-29 fixing the Rdy pin
2022-08-30 adding an octal register and updating the Rdy pin on the SIPO to Clock XOR Half
2022-08-30 fix: set -e in makefile, spelling
2022-10-12 I guess this is what's on my programmable chips currently
2022-10-16 wip: horizontal control stability
2022-10-17 trying to make an 8 bit counter but galasm is mad
2022-10-21 adding 8 and 10 bit counters on the 22v10 and 16v8
2022-10-25 wip(gal): vertical control stability
2022-10-25 wip(eeprom): schematic for sync circuit
2022-10-27 fix(sync): /LOAD is active low, don't ground it
    Previously, all the /LOAD pins (/PE on the diagram) were wired to ground,
    but the intention was to disable the "preloading" feature entirely, which
    this change accomplishes by tying them high instead.
2022-10-30 small program to generate the timing binary file to be loaded into the eeprom
2022-10-30 adding readme
2022-10-30 gitignore
2022-10-31 debugging and timing.dat updates
2022-11-01 wip: analyze for robogen
2022-11-01 wip(eeprom): move ~{RESET}, update bits->pins
2022-12-18 wip: proof-of-concept for "robosim"
    A "discrete event simulator" model of our circuit(s) so we can ask
    questions like "which invariants are we violating?" and maybe even
    "what did we decide to do about the SPI clock? why?"
2022-12-20 wip(does-not-compile): trying to wire up a network
    Attempting to connect an inverter that will delay changing its output
    by 6ns to my 80MHz clock, but Rust does not believe what I'm doing is
    safe. Maybe it even isn't?
2022-12-20 chore: move experimental (dead) code
2022-12-20 wip(fix): restrict wire1 inputs to unitary, poorly
    In order to achieve the goal of 2c94850 without too much wrangling, we
    restrict things that are inputs into a node to only produce a single
    future scheduled event so we can avoid needing to possibly call
    downstream consumers more than once in the future.
    Alternatives include:
    * Possibly restricting consumers to being Fn (vs FnMut), and passing
2023-01-11 robogen using bitflags and the timing sequence now generates a START signal to tell the cpu to begin processing the frame. robogen also structures the bits as active high, and only at the end flippin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
2023-01-31 updated SIPO mostly
2023-01-31 updating robogen timing upload command in readme
2023-02-02 adding vga hardware schematics
2023-02-02 svg schematics as pdf and svg
2023-02-06 schematic updated
2023-02-06 keyboard discussion
2023-04-26 vga schematic and pcb layout
2023-04-30 reset pin added to SIPO
2023-05-02 making a timing circuit PCB
2023-05-06 cpu data pcb
2023-05-17 cpu data now uses RC circuits for timing instead of not gates
2023-05-20 cpu data board has transistor included
2023-05-26 finalized form of pcb and schematic
2023-05-26 retracing some lines and taking out several vias, making all smd caps and Rs to be the same footprint size
2023-06-09 adding the socket footprint
2023-06-12 routing completed
2023-06-18 labels on the back of the board, layout and retraced, labels on front of board
2023-06-23 updating gal to include the pixel clk output as expressed in the scchematic
2023-06-28 added power and pixel indicator LEDs, rearranged and changed some headers for clearance of the GAL, fixed a location issue with a decoup cap
2023-06-30 gnd-ing the /OE on the gal
2023-08-11 updating board to use clocked latches as the data mile markers instead of RC time circuits. Also adding a clock board breadboardable circuit module
2023-09-08 final board
2023-09-09 fix: line up gal with board
2023-09-10 updating eeprom and robogen to invert start_frame
